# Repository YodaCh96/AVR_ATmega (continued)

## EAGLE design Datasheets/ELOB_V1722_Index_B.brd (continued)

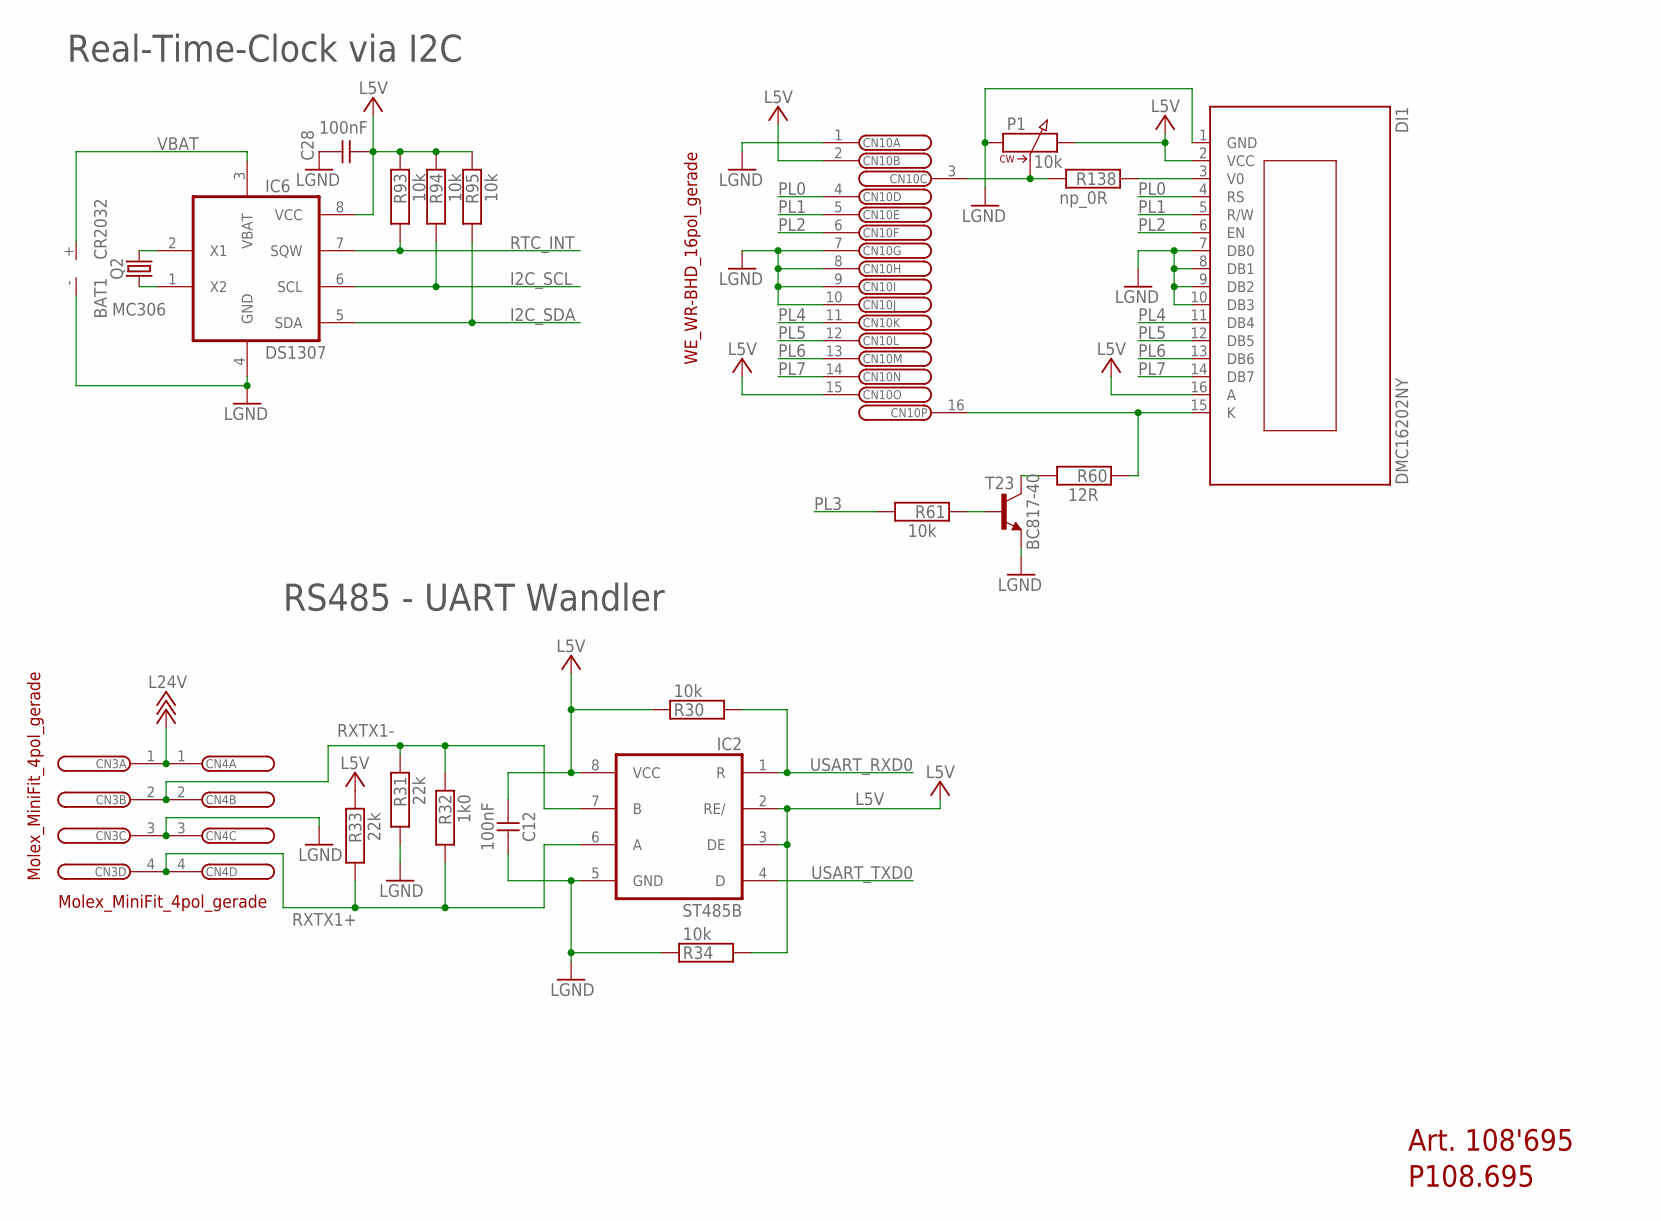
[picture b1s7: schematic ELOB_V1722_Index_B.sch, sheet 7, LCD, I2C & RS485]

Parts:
BAT1: CR2032; CR2032SMT_WÜRTH
C12, C28: 100nF; C0603
CN3, CN4: Molex_MiniFit_4pol_gerade; MOLEX_MINIFIT_4G
CN10: WE_WR-BHD_16pol_gerade; BH_16G
DI1: DMC16202NY; DISPLAY_DMC16202NY-LY-AZE-BJN
IC2: ST485B; SO_08
IC6: DS1307; SO_08
P1: 10k; POTI_MURATA_PVG3A
Q2: MC306
R30, R34, R61, R93, R94, R95: 10k; R0603
R31, R33: 22k; R0603
R32: 1k0; R0603
R60: 12R; R0603
R138: np_0R; R1206
T23: BC817-40; SOT23-BEC

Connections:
I2C_SCL: IC6.6 (SCL), R94.2; also elsewhere on the board
I2C_SDA: IC6.5 (SDA), R95.2; also elsewhere on the board
L5V: C12.1, C28.2, CN10.2, CN10.15, DI1.2 (VCC), DI1.16 (A), IC2.2 (RE/), IC2.3 (DE), IC2.8 (VCC), IC6.8 (VCC), P1.3 (2), R30.1, R33.1, R34.2, R93.1, R94.1, R95.1; also elsewhere on the board
L24V: CN3.1, CN4.1; also elsewhere on the board
LGND: BAT1.-, C12.2, C28.1, CN3.3, CN4.3, CN10.1, CN10.7, CN10.8, CN10.9, CN10.10, DI1.1 (GND), DI1.7 (DB0), DI1.8 (DB1), DI1.9 (DB2), DI1.10 (DB3), IC2.5 (GND), IC6.4 (GND), P1.1, R31.2, R34.1, T23.2 (E); also elsewhere on the board
unnamed: CN10.3, P1.2 (S), R138.2
unnamed: CN10.16, DI1.15 (K), R60.1
unnamed: R61.1, T23.1 (B)
unnamed: IC6.1 (X2), Q2.1
unnamed: DI1.3 (V0), R138.1
unnamed: IC6.2 (X1), Q2.4 (2)
unnamed: R60.2, T23.3 (C)
PL0: CN10.4, DI1.4 (RS); also elsewhere on the board
PL1: CN10.5, DI1.5 (R/W); also elsewhere on the board
PL2: CN10.6, DI1.6 (EN); also elsewhere on the board
PL3: R61.2; also elsewhere on the board
PL4: CN10.11, DI1.11 (DB4); also elsewhere on the board
PL5: CN10.12, DI1.12 (DB5); also elsewhere on the board
PL6: CN10.13, DI1.13 (DB6); also elsewhere on the board
PL7: CN10.14, DI1.14 (DB7); also elsewhere on the board
RTC_INT: IC6.7 (SQW), R93.2; also elsewhere on the board
RXTX1+: CN3.4, CN4.4, IC2.6 (A), R32.2, R33.2
RXTX1-: CN3.2, CN4.2, IC2.7 (B), R31.1, R32.1
USART_RXD0: IC2.1 (R), R30.2; also elsewhere on the board
USART_TXD0: IC2.4 (D); also elsewhere on the board
VBAT: BAT1.+, IC6.3 (VBAT)

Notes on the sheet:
Art. 108'695
P108.695
Real-Time-Clock via I2C
RS485 - UART Wandler

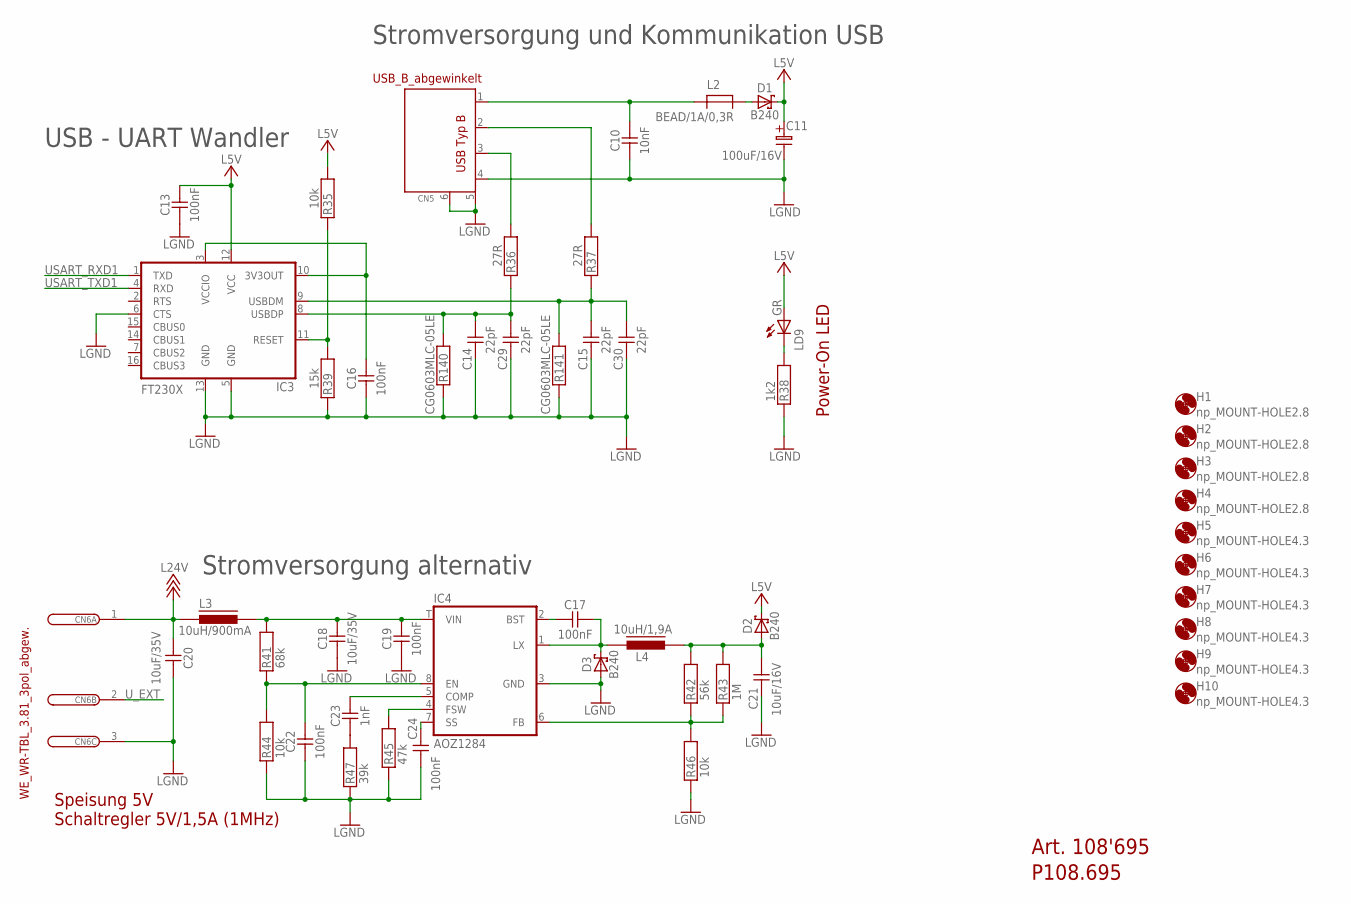
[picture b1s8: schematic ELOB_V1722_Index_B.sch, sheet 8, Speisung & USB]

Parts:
C10: 10nF; C0603
C11: 100uF/16V; ELKO_SMD_6.3
C13, C16, C17, C19, C22, C24: 100nF; C0603
C14, C15, C29, C30: 22pF; C0603
C18, C20: 10uF/35V; C1206
C21: 10uF/16V; C1206
C23: 1nF; C0603
CN5: USB_B_abgewinkelt; USB-B
CN6: WE_WR-TBL_3.81_3pol_abgew.; PHOENIX_G381_3
D1, D2, D3: B240; SMA
H1, H2, H3, H4: np_MOUNT-HOLE2.8; 2,8
H5, H6, H7, H8, H9, H10: np_MOUNT-HOLE4.3; 4,3
IC3: FT230X; SSOP16
IC4: AOZ1284; SO-8_EP_AOS
L2: BEAD/1A/0,3R; R1206
L3: 10uH/900mA; L1210
L4: 10uH/1,9A; INDUCTOR_NR6028
LD9: GR; LED_0805
R35, R44, R46: 10k; R0603
R36, R37: 27R; R0603
R38: 1k2; R0603
R39: 15k; R0603
R41: 68k; R0603
R42: 56k; R0603
R43: 1M; R0603
R45: 47k; R0603
R47: 39k; R0603
R140, R141: CG0603MLC-05LE; R0603

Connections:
L5V: C11.P, C13.1, D1.C, D2.C, IC3.12 (VCC), LD9.A, R35.2; also elsewhere on the board
L24V: C20.1, CN6.1, L3.1; also elsewhere on the board
LGND: C10.2, C11.M, C13.2, C14.2, C15.2, C16.2, C18.2, C19.2, C20.2, C21.2, C22.2, C24.2, C29.2, C30.2, CN5.4, CN5.5, CN5.6, CN6.3, D3.A, IC3.5 (GND), IC3.6 (CTS), IC3.13 (GND), IC4.3 (GND), R38.1, R39.1, R44.1, R45.1, R46.1, R47.1, R140.1, R141.1; also elsewhere on the board
unnamed: C17.2, D3.C, IC4.1 (LX), L4.1
unnamed: C24.1, IC4.7 (SS)
unnamed: D1.A, L2.2
unnamed: IC4.4 (FSW), R45.2
unnamed: C23.1, IC4.5 (COMP)
unnamed: C23.2, R47.2
unnamed: C18.1, C19.1, IC4.T (VIN), L3.2, R41.2
unnamed: C22.1, IC4.8 (EN), R41.1, R44.2
unnamed: IC4.6 (FB), R42.1, R43.1, R46.2
unnamed: C17.1, IC4.2 (BST)
unnamed: C21.1, D2.A, L4.2, R42.2, R43.2
unnamed: IC3.11 (RESET), R35.1, R39.2
unnamed: LD9.K (C), R38.2
unnamed: C10.1, CN5.1, L2.1
unnamed: C15.1, C30.1, IC3.9 (USBDM), R37.1, R141.2
unnamed: CN5.2, R37.2
unnamed: C14.1, C29.1, IC3.8 (USBDP), R36.1, R140.2
unnamed: C16.1, IC3.3 (VCCIO), IC3.10 (3V3OUT)
unnamed: CN5.3, R36.2
USART_RXD1: IC3.1 (TXD); also elsewhere on the board
USART_TXD1: IC3.4 (RXD); also elsewhere on the board
U_EXT: CN6.2; also elsewhere on the board

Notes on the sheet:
Speisung 5V
Schaltregler 5V/1,5A (1MHz)
Stromversorgung alternativ
Power-On LED
Stromversorgung und Kommunikation USB
USB - UART Wandler
Art. 108'695
P108.695

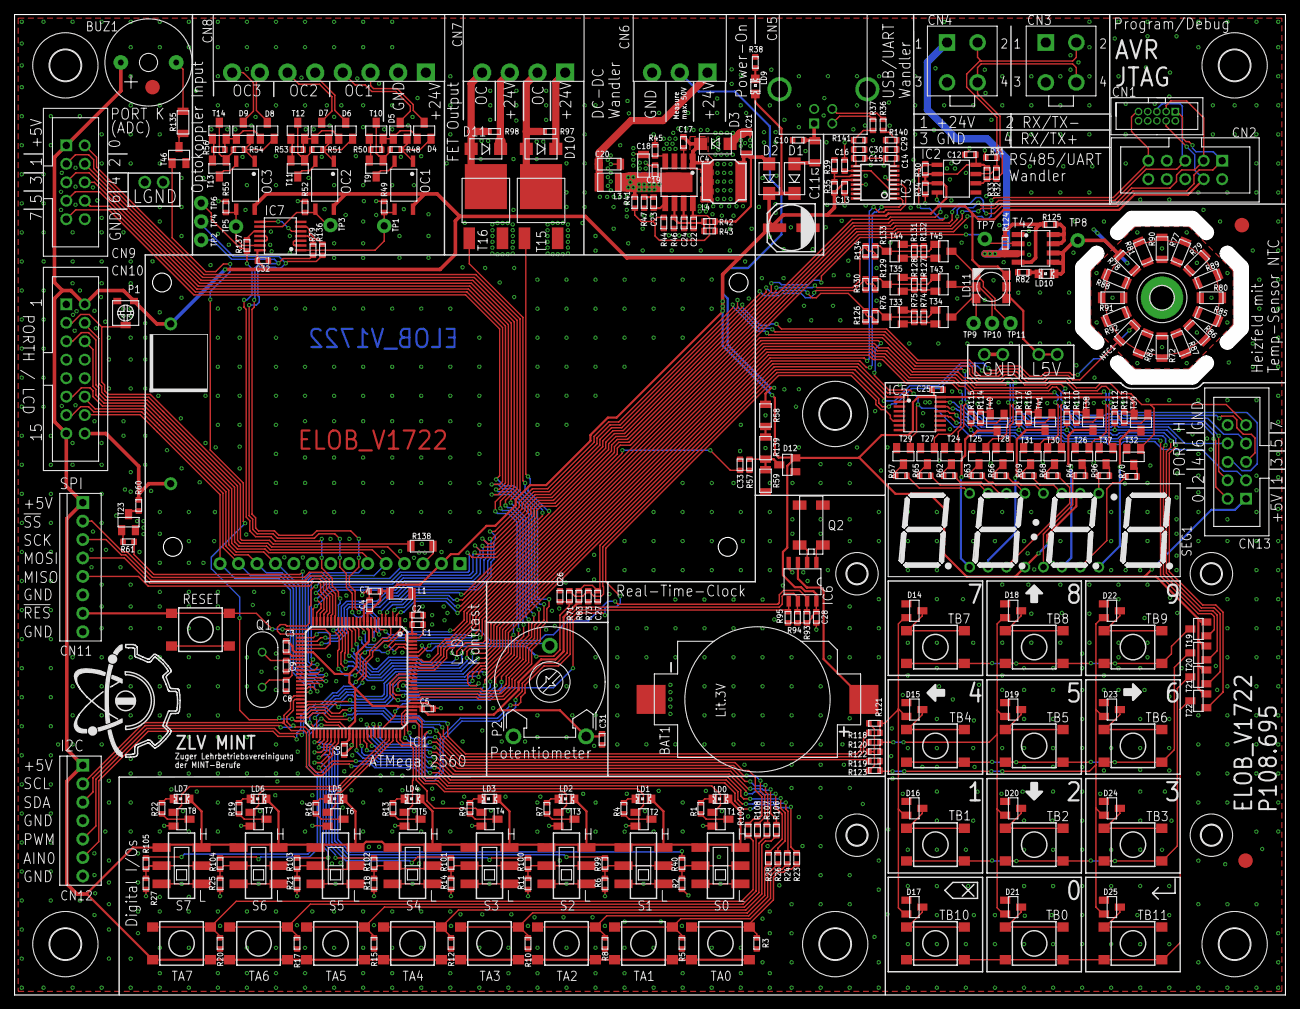
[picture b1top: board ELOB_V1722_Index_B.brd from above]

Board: 2 copper layers, 173.0 x 133.0 mm, 346 parts (0 on the bottom side), 257 nets.

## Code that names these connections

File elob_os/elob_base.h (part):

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
#define  SEG7_SELDDR   (DDRG)
#define  SEG7_SELPORT  (PORTG)
#define  SEG7_0        (PG0)
#define  SEG7_1        (PG1)
#define  SEG7_EN       (PG2)
#define  SEG7_GRAD     (PG3)
#define  SEG7_COLON    (PG4)

#define  SEG7_DIGIDDR  (DDRH)
#define  SEG7_DIGIPORT (PORTH)

#define  KEYB_INPORTDDR  (DDRD)
#define  KEYB_INPORT     (PORTD)
#define  KEYB_INMASK     ((1<<PD4)|(1<<PD5)|(1<<PD6))
#define  KEYB_INMASKSHIFT (4)

// The RGB Led's are connects on 
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/**
 * @brief  The buzzer() was started and the time is now reach zero
*/
#define EVENT_BUZZER_OFF    (0x50)  // the buzzer has finished



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/**
 * @brief    ADC multiplexer channel for the on board NTC
 */
#define ADC_NTC  (2)       // ADC mux input for ntc


/**
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
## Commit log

2021-02-15 chore: update AVR files
2021-02-15 test: rename the AVR files
2021-02-16 test: remove files
